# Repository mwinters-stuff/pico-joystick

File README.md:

# vscode-devcontainer-raspberrypi-pico

## Usage

Clone or download repository, copy the contents of .devcontainer into your project
Remove any existing "build" directory.

Open the folder, and allow the container to build.

# To know
* SDK is installed in /pico-sdk
* All USB devices are exported to container - so the picoprobe can be found and used.
* USB Device /dev/ttyACM0 is exported to container for monitoring

## This container includes
* pico-sdk
* openocd - compiled for picoprobe
* picotool
* bootterm (for serial monitoring) - see https://github.com/wtarreau/bootterm

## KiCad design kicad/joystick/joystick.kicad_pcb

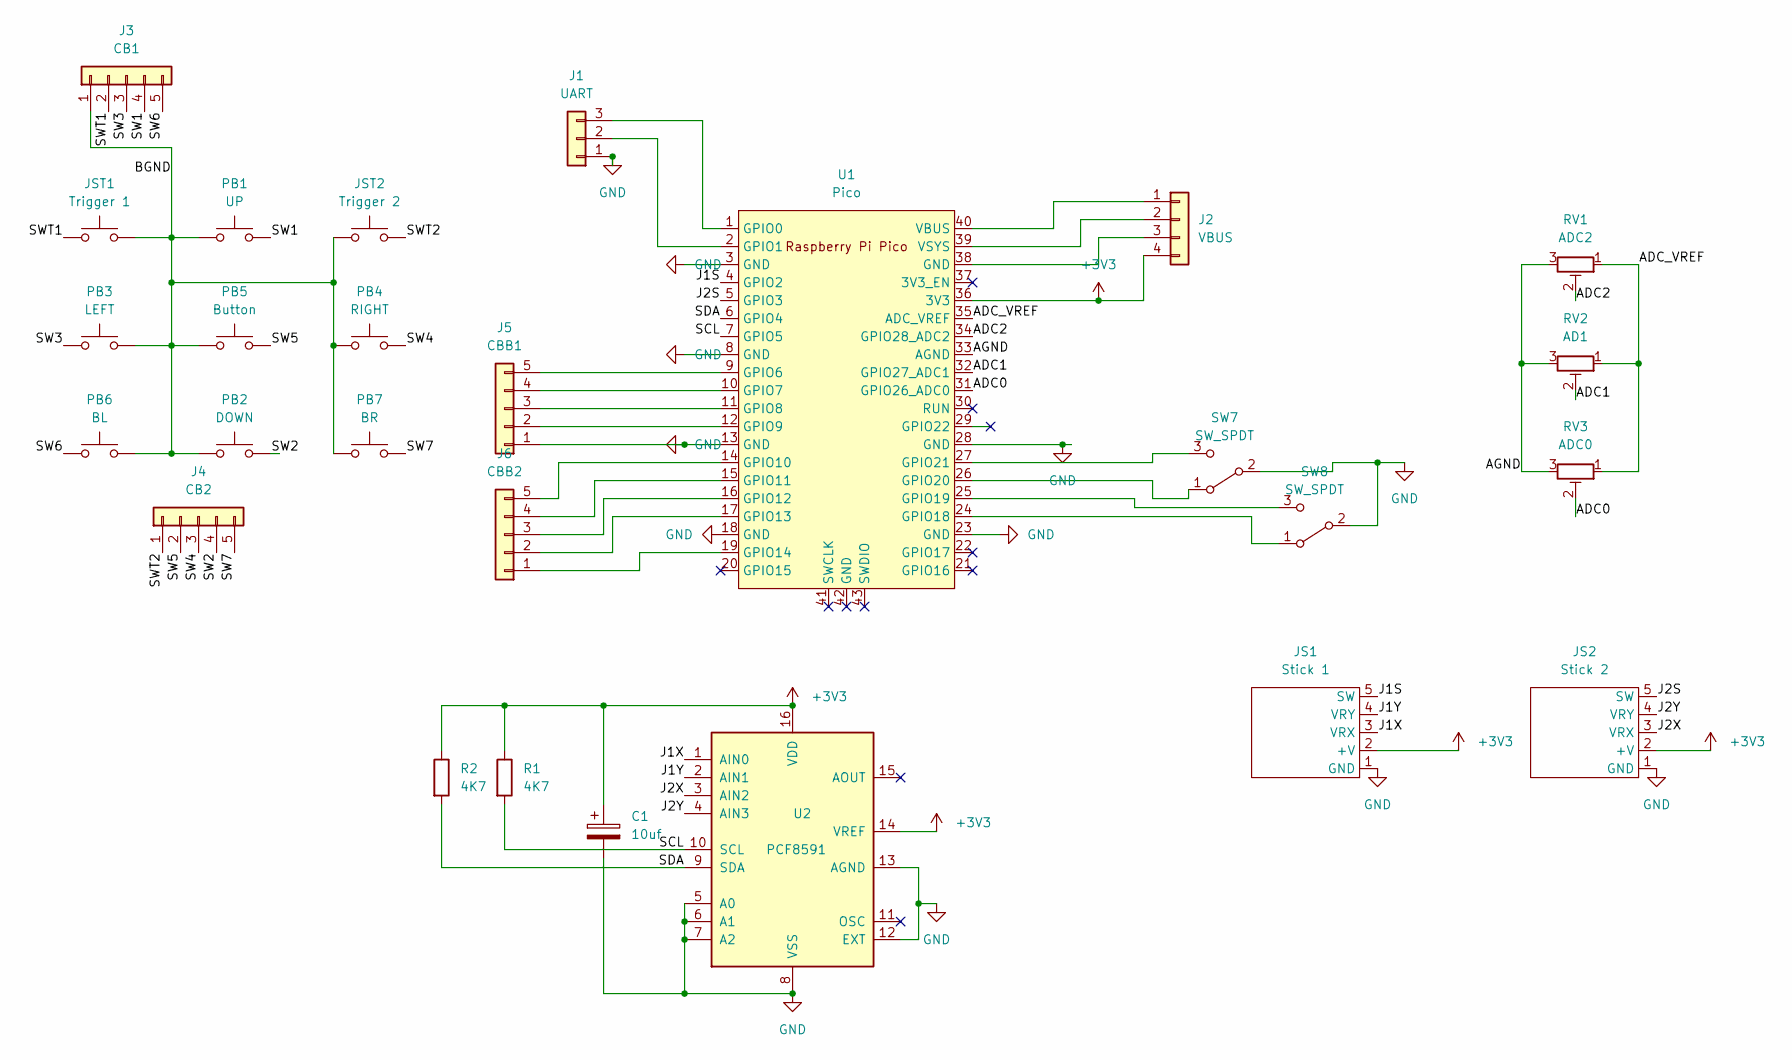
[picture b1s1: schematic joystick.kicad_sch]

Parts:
C1: 10uf; CP_Radial_D5.0mm_P2.50mm
J1: UART; PinHeader_1x03_P2.54mm_Vertical
J2: VBUS; PinHeader_1x04_P2.54mm_Vertical
J3: CB1; PinHeader_1x05_P2.54mm_Vertical
J4: CB2; PinHeader_1x05_P2.54mm_Vertical
J5: CBB1; PinSocket_1x05_P2.54mm_Vertical
J6: CBB2; PinSocket_1x05_P2.54mm_Vertical
JS1: Stick 1; Joystick
JS2: Stick 2; Joystick
JST1: Trigger 1; SW_PUSH_6mm_SP
JST2: Trigger 2; SW_PUSH_6mm_SP
PB1: UP; SW_PUSH_6mm_SP
PB2: DOWN; SW_PUSH_6mm_SP
PB3: LEFT; SW_PUSH_6mm_SP
PB4: RIGHT; SW_PUSH_6mm_SP
PB5: Button; SW_PUSH_6mm_SP
PB6: BL; SW_PUSH_6mm_SP
PB7: BR; SW_PUSH_6mm_SP
R1, R2: 4K7; R_Axial_DIN0207_L6.3mm_D2.5mm_P10.16mm_Horizontal
RV1: ADC2; Potentiometer_Runtron_RM-065_Vertical
RV2: AD1; Potentiometer_Runtron_RM-065_Vertical
RV3: ADC0; Potentiometer_Runtron_RM-065_Vertical
SW7, SW8: SW_SPDT; PinHeader_1x03_P2.54mm_Vertical
U1: Pico; RPi_Pico_SMD_TH
U2: PCF8591; DIP-16_W7.62mm

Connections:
+3V3: C1.1, J2.4, JS1.2 (+V), JS2.2 (+V), R1.1, R2.1, U1.36 (3V3), U2.14 (VREF), U2.16 (VDD)
/ADC0: RV3.2, U1.31 (GPIO26_ADC0)
/ADC1: RV2.2, U1.32 (GPIO27_ADC1)
/ADC2: RV1.2, U1.34 (GPIO28_ADC2)
/ADC_VREF: RV1.1, RV2.1, RV3.1, U1.35 (ADC_VREF)
/AGND: RV1.3, RV2.3, RV3.3, U1.33 (AGND)
/BGND: J3.1, JST1.2, JST2.1, PB1.1, PB2.1, PB3.2, PB4.1, PB5.1, PB6.2, PB7.1
/J1S: JS1.5 (SW), U1.4 (GPIO2)
/J1X: JS1.3 (VRX), U2.1 (AIN0)
/J1Y: JS1.4 (VRY), U2.2 (AIN1)
/J2S: JS2.5 (SW), U1.5 (GPIO3)
/J2X: JS2.3 (VRX), U2.3 (AIN2)
/J2Y: JS2.4 (VRY), U2.4 (AIN3)
/SCL: R1.2, U1.7 (GPIO5), U2.10 (SCL)
/SDA: R2.2, U1.6 (GPIO4), U2.9 (SDA)
/SW1: J3.4, PB1.2
/SW2: J4.4, PB2.2
/SW3: J3.3, PB3.1
/SW4: J4.3, PB4.2
/SW5: J4.2, PB5.2
/SW6: J3.5, PB6.1
/SW7: J4.5, PB7.2
/SWT1: J3.2, JST1.1
/SWT2: J4.1, JST2.2
GND: C1.2, J1.1, J5.1, JS1.1 (GND), JS2.1 (GND), SW7.2 (B), SW8.2 (B), U1.3 (GND), U1.8 (GND), U1.13 (GND), U1.18 (GND), U1.23 (GND), U1.28 (GND), U2.5 (A0), U2.6 (A1), U2.7 (A2), U2.8 (VSS), U2.12 (EXT), U2.13 (AGND)
unnamed: J1.2, U1.2 (GPIO1)
unnamed: J1.3, U1.1 (GPIO0)
unnamed: J5.2, U1.12 (GPIO9)
unnamed: J5.3, U1.11 (GPIO8)
unnamed: J5.4, U1.10 (GPIO7)
unnamed: J5.5, U1.9 (GPIO6)
unnamed: J6.1, U1.19 (GPIO14)
unnamed: J6.2, U1.17 (GPIO13)
unnamed: J6.3, U1.16 (GPIO12)
unnamed: J6.4, U1.15 (GPIO11)
unnamed: J6.5, U1.14 (GPIO10)
unnamed: SW7.1 (A), U1.26 (GPIO20)
unnamed: SW7.3 (C), U1.27 (GPIO21)
unnamed: SW8.1 (A), U1.24 (GPIO18)
unnamed: SW8.3 (C), U1.25 (GPIO19)
unnamed: J2.3, U1.38 (GND)
unnamed: J2.2, U1.39 (VSYS)
unnamed: J2.1, U1.40 (VBUS)

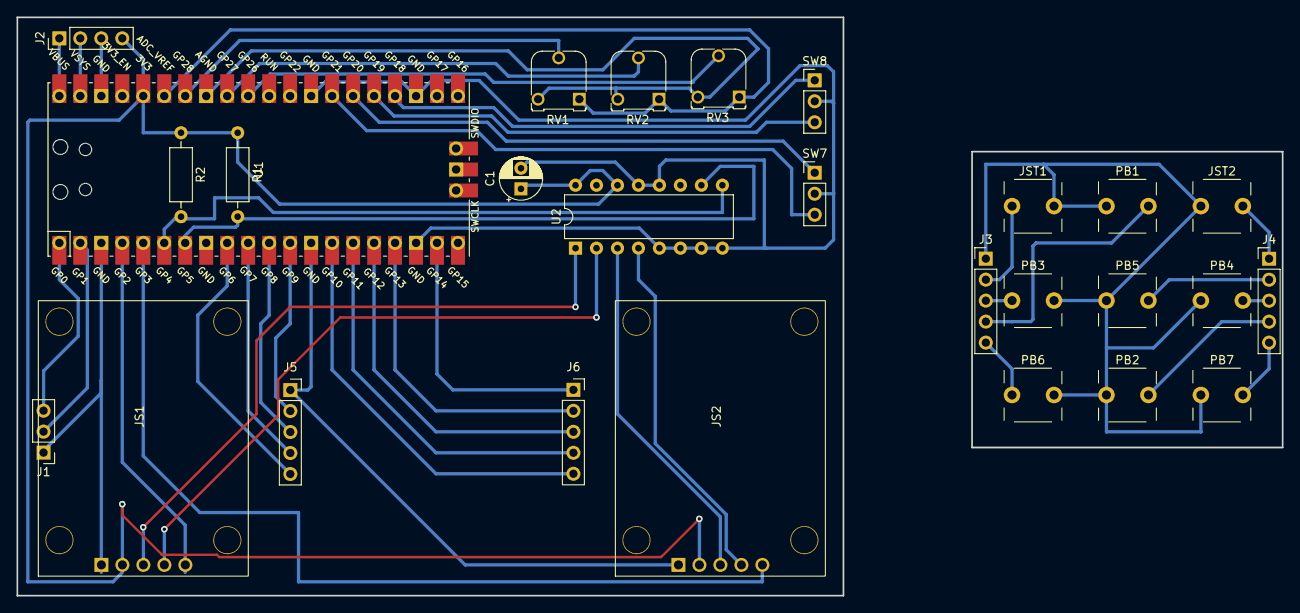
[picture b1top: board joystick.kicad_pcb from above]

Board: 2 copper layers, 153.2 x 70.0 mm, 27 parts (0 on the bottom side), 43 nets.

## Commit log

2022-11-30 Initial Commitg
2022-12-01 Working ish gamepad.
2022-12-01 add usb serial console
2022-12-01 Atttempt at 2 joysticks
2022-12-08 two joysticks working.
2022-12-11 working as 1 or two joysticks or gamepad.
